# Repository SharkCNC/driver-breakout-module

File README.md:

### IMPORTANT!  This board is under development, reproducing it will be at your own risk.

# driver-breakout-module
This breakout board makes it possible to connect the SharkCNC motherboard and the drivers using shielded RJ45 cable.

<the board is already being produced, soon real photos>

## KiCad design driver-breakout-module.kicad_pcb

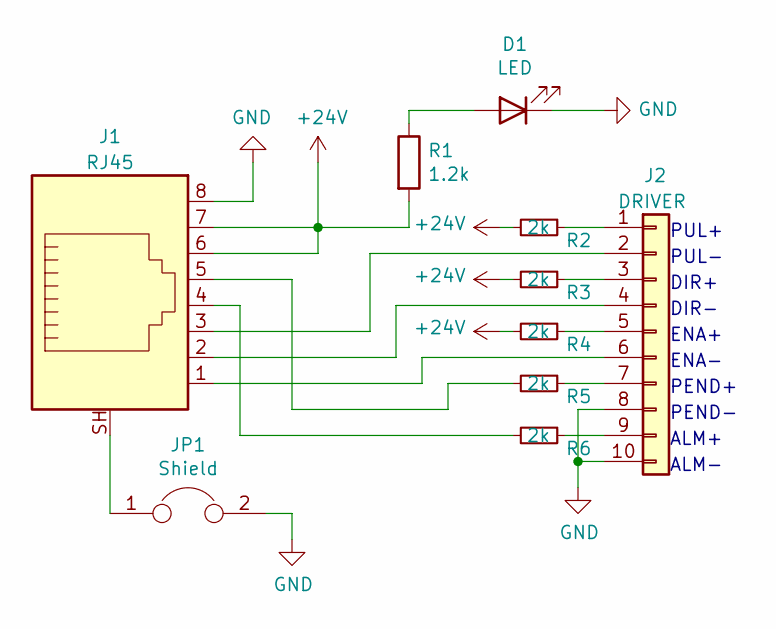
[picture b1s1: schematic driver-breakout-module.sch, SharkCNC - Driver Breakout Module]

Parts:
D1: LED; LED_0805_2012Metric
J1: RJ45; RJ45_Ninigi_GE
J2: DRIVER; PinHeader_1x10_P5.08mm_Vertical
JP1: Shield; PinHeader_1x02_P2.54mm_Vertical
R1: 1.2k; R_0805_2012Metric
R2, R3, R4, R5, R6: 2k; R_0805_2012Metric

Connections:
+24V: J1.6, J1.7, R1.2, R2.2, R3.2, R4.2
GND: D1.1 (K), J1.8, J2.8, J2.10, JP1.2
unnamed: D1.2 (A), R1.1
unnamed: J1.1, J2.6
unnamed: J1.2, J2.4
unnamed: J1.3, J2.2
unnamed: J1.4, R6.2
unnamed: J1.5, R5.2
unnamed: J1.SH, JP1.1
unnamed: J2.1, R2.1
unnamed: J2.3, R3.1
unnamed: J2.5, R4.1
unnamed: J2.7, R5.1
unnamed: J2.9, R6.1

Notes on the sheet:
PUL+
PUL-
DIR+
DIR-
ENA+
ENA-
PEND+
PEND-
ALM+
ALM-

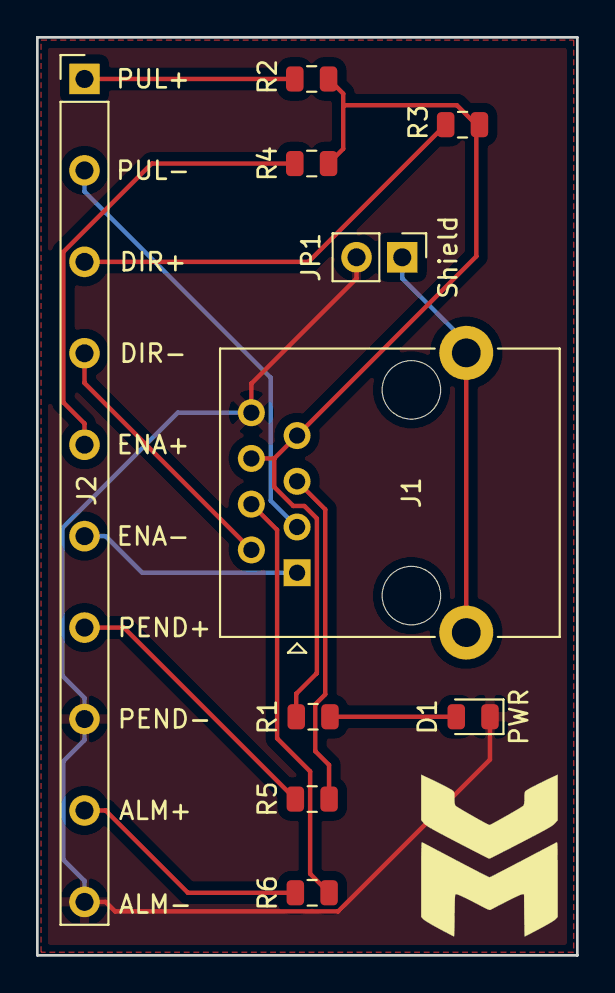
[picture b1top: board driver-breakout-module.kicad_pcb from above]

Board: 2 copper layers, 30.0 x 51.0 mm, 10 parts (0 on the bottom side), 14 nets.

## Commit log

2020-07-12 Add first version
2020-07-13 Update Readme file
